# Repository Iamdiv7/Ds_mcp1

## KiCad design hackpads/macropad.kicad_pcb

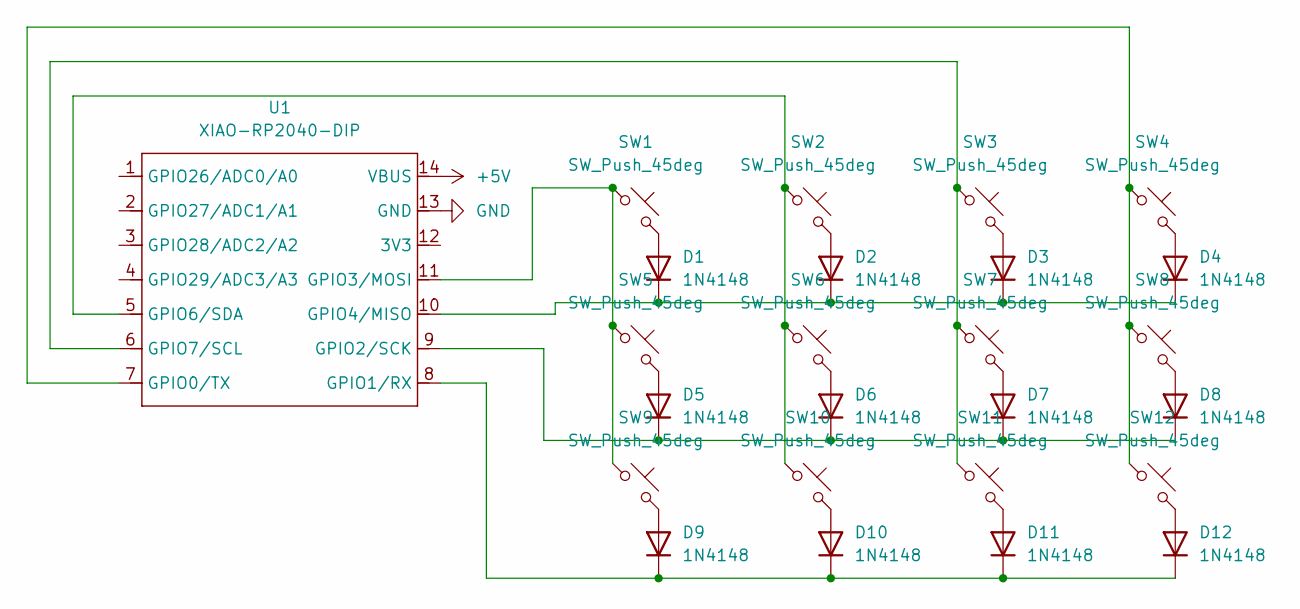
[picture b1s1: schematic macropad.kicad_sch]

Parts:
D1, D2, D3, D4, D5, D6, D7, D8, D9, D10, D11, D12: 1N4148; D_DO-35_SOD27_P7.62mm_Horizontal
SW1, SW2, SW3, SW4, SW5, SW6, SW7, SW8, SW9, SW10, SW11, SW12: SW_Push_45deg; SW_Cherry_MX_1.00u_PCB
U1: XIAO-RP2040-DIP

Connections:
+5V: U1.14 (VBUS)
GND: U1.13 (GND)
unnamed: D1.2 (A), SW1.2
unnamed: D1.1 (K), D2.1 (K), D3.1 (K), D4.1 (K), U1.10 (GPIO4/MISO)
unnamed: D2.2 (A), SW2.2
unnamed: D3.2 (A), SW3.2
unnamed: D4.2 (A), SW4.2
unnamed: D5.2 (A), SW5.2
unnamed: D5.1 (K), D6.1 (K), D7.1 (K), D8.1 (K), U1.9 (GPIO2/SCK)
unnamed: D6.2 (A), SW6.2
unnamed: D7.2 (A), SW7.2
unnamed: D8.2 (A), SW8.2
unnamed: D9.2 (A), SW9.2
unnamed: D10.2 (A), SW10.2
unnamed: D9.1 (K), D10.1 (K), D11.1 (K), D12.1 (K), U1.8 (GPIO1/RX)
unnamed: D11.2 (A), SW11.2
unnamed: D12.2 (A), SW12.2
unnamed: SW4.1, SW8.1, SW12.1, U1.7 (GPIO0/TX)
unnamed: SW1.1, SW5.1, SW9.1, U1.11 (GPIO3/MOSI)
unnamed: SW2.1, SW6.1, SW10.1, U1.5 (GPIO6/SDA)
unnamed: SW3.1, SW7.1, SW11.1, U1.6 (GPIO7/SCL)

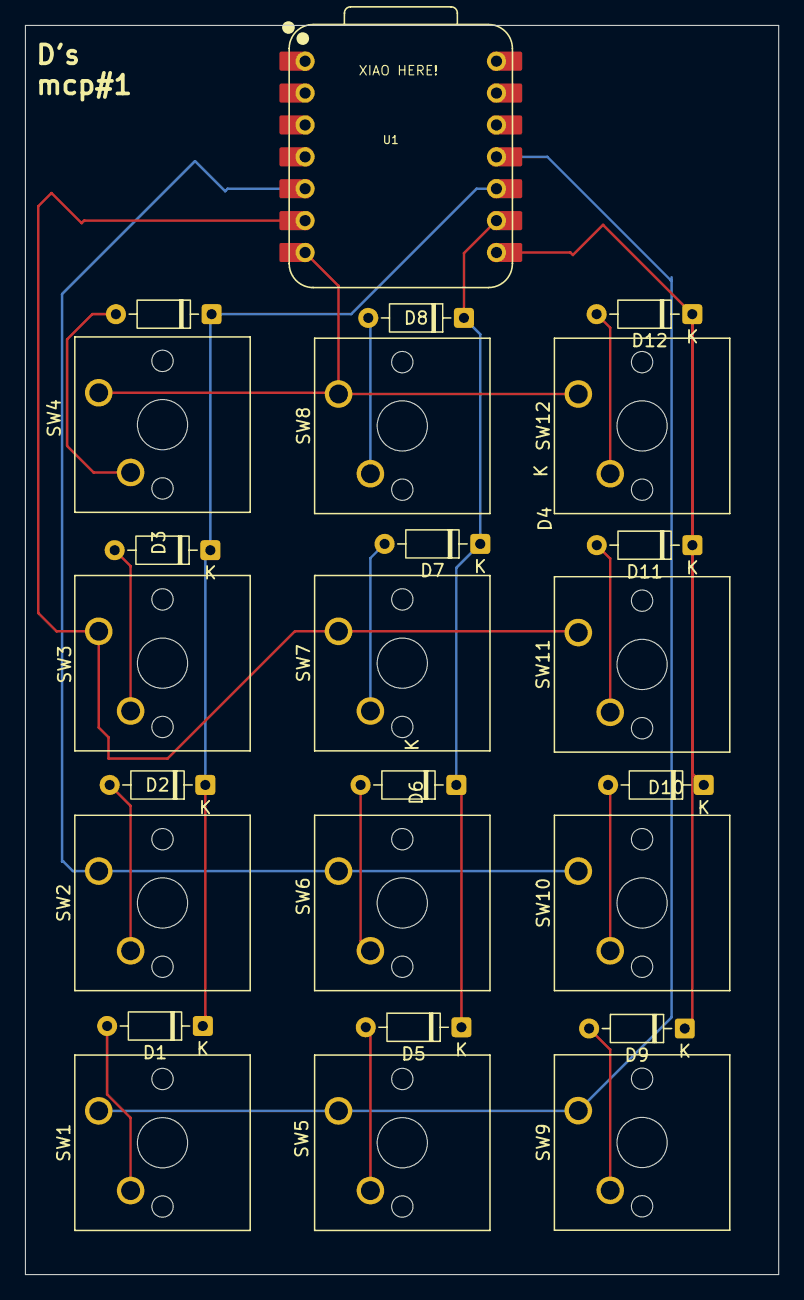
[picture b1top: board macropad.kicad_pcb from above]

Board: 2 copper layers, 60.0 x 99.5 mm, 25 parts (0 on the bottom side), 19 nets.

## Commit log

2025-06-24 3D designed case files
2025-06-24 pcb files
2025-06-24 Rename hackpads/bottom case.3mf to hackpads/D's mcp#1/CAD/bottom case.3mf
2025-06-24 Rename hackpads/macropad.kicad_pro to hackpads/D's mcp#1/PCB Files/macropad.kicad_pro
2025-06-24 Gerber files
2025-06-24 Rename hackpads/D's mcp#1/gerber.zip to hackpads/D's mcp#1/Production files/gerber.zip
2025-06-24 case files
2025-06-24 kmk code
2025-06-24 Update KMK
2025-06-24 the PROPER case file w/ pcb's 3D model.
2025-06-26 READ.ME
2025-06-26 Rename READ.ME to README.md
2025-06-26 Rename hackpads/D's mcp#1/PCB_design.png to hackpads/D's mcp#1/pics/PCB_design.png
2025-06-26 Rename hackpads/D's mcp#1/Schematic_design.png to hackpads/D's mcp#1/pics/Schematic_design.png
2025-06-26 Rename hackpads/D's mcp#1/case_design.png to hackpads/D's mcp#1/pics/case_design.png
2025-06-26 Rename hackpads/D's mcp#1/fullmcp.png to hackpads/D's mcp#1/pics/fullmcp.png
2025-06-27 Rename PCB_design.png to WRONG_PCB_design.png
